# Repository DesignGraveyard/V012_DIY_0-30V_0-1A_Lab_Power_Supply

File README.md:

# Description

Build a cheap and reliable 0–30V, 0–1A bench power supply using standard components like the LM317 and NE555. 
This design is based on a ON-Semiconductors application note but simplified with common “jellybean” parts and a NE555 charge pump to generate the negative voltage reference to achieve output control down to 0 Volt & 0 Ampere.

The video below shows the power supply in action, assembly tips, how to manage the thermals, a LM317 offline HTML tool including losses and an explanation how it works!

# Check out the video:

# Schematic of the power supply

# PCB Connections of the power supply PCBA:  

#  Offline LM317 calculator tool, including losses: 

# Files:  
  
-PCB Gerber files to order the PCBs: (PCB_GERBER_V011_LM317_Lab_power_supply_0-30V.zip).  
-KiCAD 10 Files: PCB source files to adapt the design.  
-LTSpice simulation: Simulation file of the full power supply, all spice models included.  
-LM317_calculator_TDG: An offline LM317 calculator tool including losses in the LM317.

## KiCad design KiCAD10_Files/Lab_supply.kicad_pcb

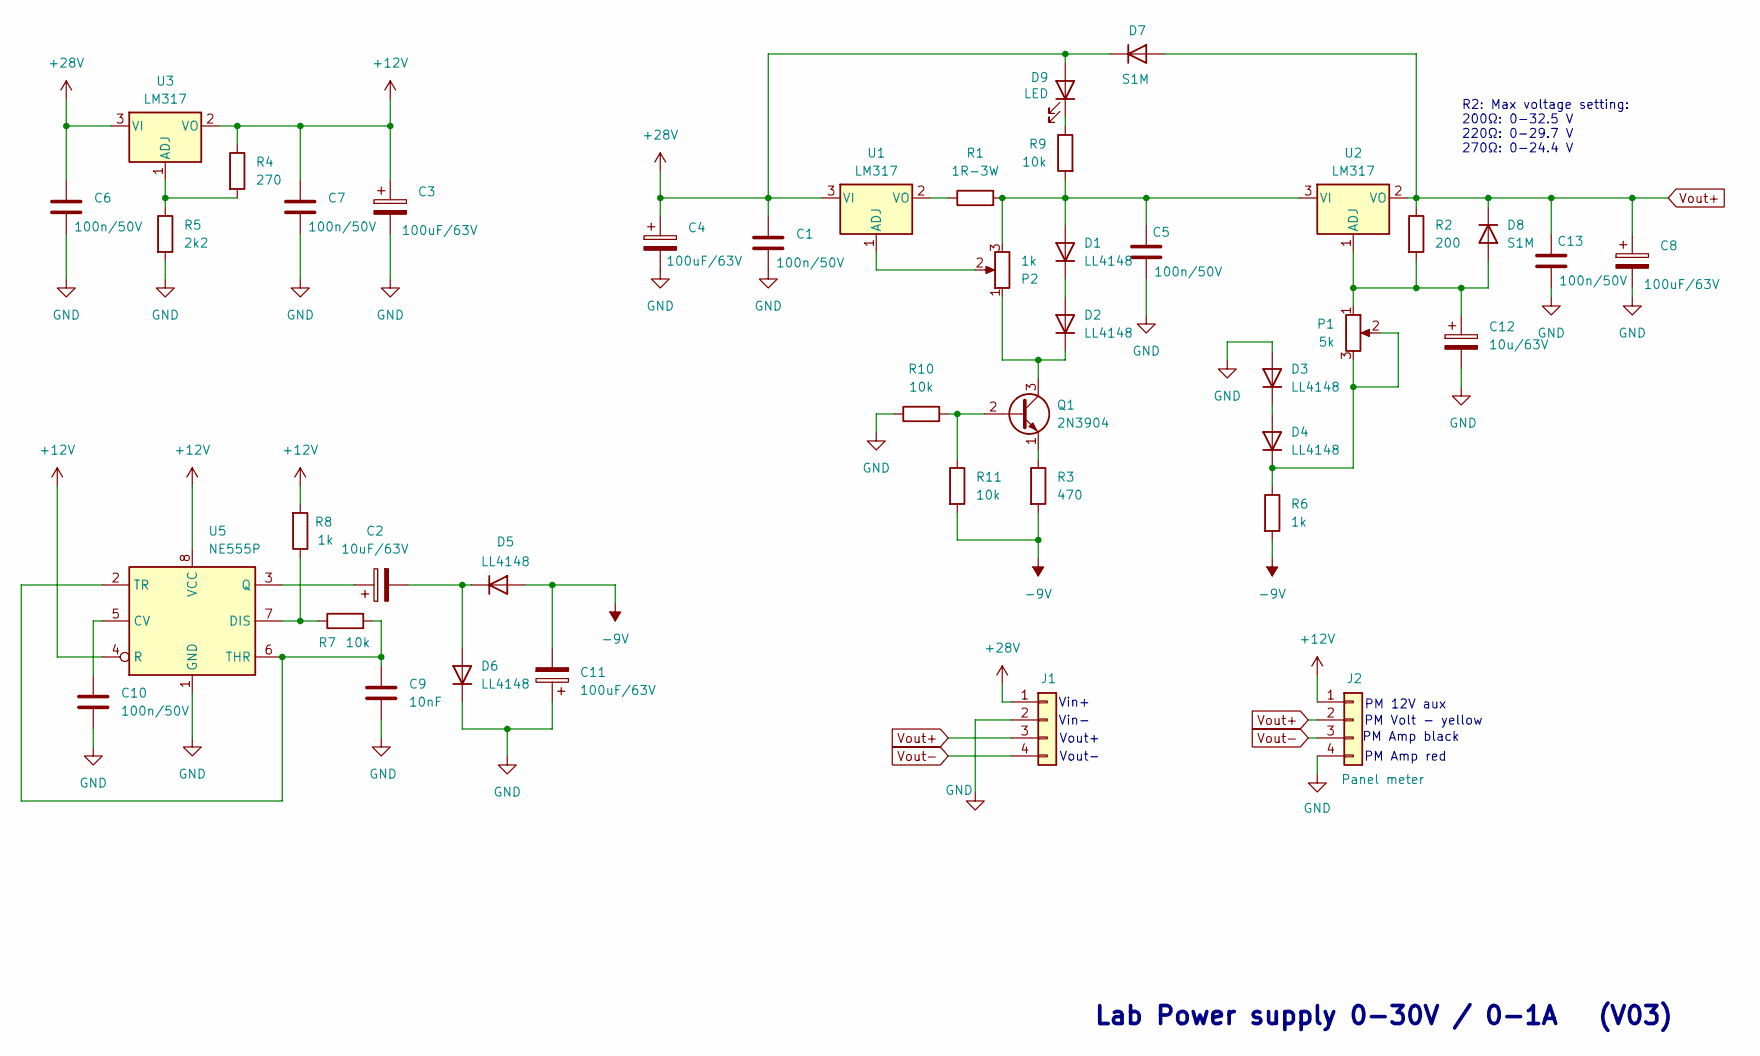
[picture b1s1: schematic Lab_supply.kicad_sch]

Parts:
C1, C5, C6, C7, C10, C13: 100n/50V; C_1206_3216Metric_Pad1.33x1.80mm_HandSolder
C2: 10uF/63V; CP_Radial_D5.0mm_P2.50mm
C3, C4, C8, C11: 100uF/63V; CP_Radial_D8.0mm_P3.50mm
C9: 10nF; C_1206_3216Metric_Pad1.33x1.80mm_HandSolder
C12: 10u/63V; CP_Radial_D5.0mm_P2.50mm
D1, D2, D3, D4, D5, D6: LL4148; D_MiniMELF
D7, D8: S1M; D_SMA
D9: LED; LED_D3.0mm_Clear
J1: in-out; SolderWire-0.5sqmm_1x04_P4.8mm_D0.9mm_OD2.3mm
J2: Panel meter; SolderWire-0.5sqmm_1x04_P4.8mm_D0.9mm_OD2.3mm
P1: 5k; Potentiometer_Alps_RK097_Single_Horizontal
P2: 1k; Potentiometer_Alps_RK097_Single_Horizontal
Q1: 2N3904; TO-92_Inline
R1: 1R-3W; R_Axial_DIN0414_L11.9mm_D4.5mm_P5.08mm_Vertical
R2: 200; R_0805_2012Metric_Pad1.20x1.40mm_HandSolder
R3: 470; R_0805_2012Metric_Pad1.20x1.40mm_HandSolder
R4: 270; R_0805_2012Metric_Pad1.20x1.40mm_HandSolder
R5: 2k2; R_0805_2012Metric_Pad1.20x1.40mm_HandSolder
R6, R8: 1k; R_0805_2012Metric_Pad1.20x1.40mm_HandSolder
R7, R10, R11: 10k; R_0805_2012Metric_Pad1.20x1.40mm_HandSolder
R9: 10k; R_1206_3216Metric_Pad1.30x1.75mm_HandSolder
U1, U2, U3: LM317; TO-220-3_Vertical
U5: NE555P; DIP-8_W7.62mm

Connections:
+12V: C3.1, C7.1, J2.1, R4.1, R8.2, U3.2 (VO), U5.4 (R), U5.8 (VCC)
+28V: C1.1, C4.1, C6.1, D7.1 (K), D9.2 (A), J1.1, U1.3 (VI), U3.3 (VI)
-9V: C11.2, D5.2 (A), R3.2, R6.2, R11.2
GND: C1.2, C3.2, C4.2, C5.2, C6.2, C7.2, C8.2, C9.2, C10.2, C11.1, C12.2, C13.2, D3.2 (A), D6.1 (K), J1.2, J2.4, R5.2, R10.1, U5.1 (GND)
unnamed: C5.1, D1.2 (A), P2.3, R1.2, R9.2, U2.3 (VI)
unnamed: D1.1 (K), D2.2 (A)
unnamed: D2.1 (K), P2.1, Q1.3 (C)
unnamed: D3.1 (K), D4.2 (A)
unnamed: D4.1 (K), P1.2, P1.3, R6.1
unnamed: C2.2, D5.1 (K), D6.2 (A)
unnamed: C12.1, D8.2 (A), P1.1, R2.2, U2.1 (ADJ)
unnamed: D9.1 (K), R9.1
unnamed: Q1.2 (B), R10.2, R11.1
unnamed: Q1.1 (E), R3.1
unnamed: P2.2, U1.1 (ADJ)
unnamed: R1.1, U1.2 (VO)
unnamed: R4.2, R5.1, U3.1 (ADJ)
unnamed: C10.1, U5.5 (CV)
unnamed: R7.1, R8.1, U5.7 (DIS)
unnamed: C2.1, U5.3 (Q)
unnamed: C9.1, R7.2, U5.2 (TR), U5.6 (THR)
Vout+: C8.1, C13.1, D7.2 (A), D8.1 (K), J1.3, J2.2, R2.1, U2.2 (VO)
Vout-: J1.4, J2.3

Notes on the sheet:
PM 12V aux
Vin+
PM Volt - yellow
Lab Power supply 0-30V / 0-1A (V03)
Vout+
Vin-
PM Amp black
Vout-
R2: Max voltage setting: 200Ω: 0-32.5 V 220Ω: 0-29.7 V 270Ω: 0-24.4 V
PM Amp red

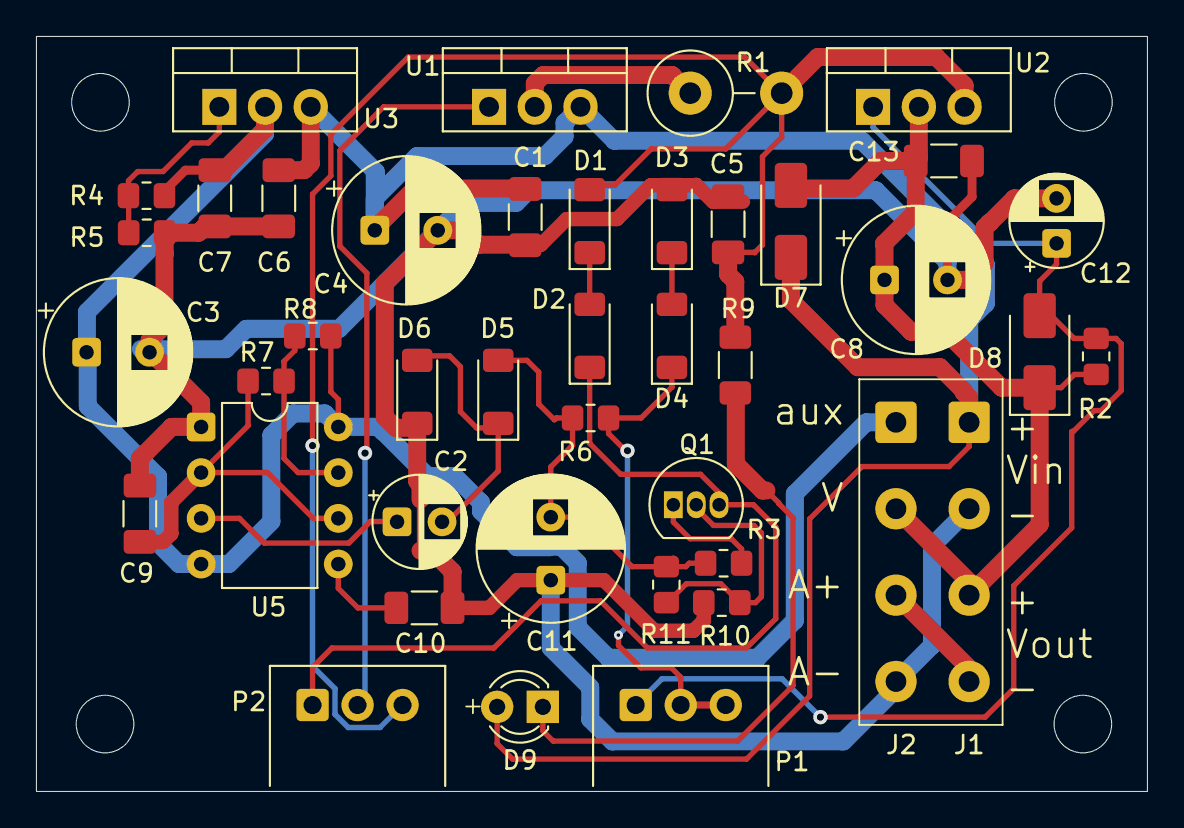
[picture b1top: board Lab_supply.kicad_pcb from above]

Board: 2 copper layers, 61.7 x 41.9 mm, 42 parts (0 on the bottom side), 23 nets.
